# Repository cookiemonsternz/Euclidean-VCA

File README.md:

# ANTANTEATEREATER

Antanteatereater is a guitar/bass effect pedal which consists of a euclidean sequencer running into a VCA. It is based around the digital HY-ESG plugin, but using an analog envelope generator and vca, as well as being in a physical format.

The euclidean sequencer runs on an MCU, in this case an arduino nano, simply because I had one lying around. The pedal has 7 controllable inputs:

-   On/Off Button
-   Tap Tempo Button (Sequencer syncs to this)
-   Envelope Attack
-   Envelope Release
-   Step (Total number of steps per cycle)
-   Pulse (Number of steps per cycle which are on)
-   Rotate (Offset of the cycle)

The project is named after the design I chose for it, which is an ant-anteater-eater, aka an ant which eats anteaters :)

### The Why -

When I make music, my absolutely most used plugin is HY-ESG. I find it super versatile and very handy for adding some rhythm to otherwise static pads and other noise. I wanted a way to use this effect in live performances, and given I don't like to have things running through my laptop on stage (due to reliability), and the fact that using it requires a lot of extra hardware, I decided to make a version of it that just worked like any regular guitar pedal.

### Pictures!

The wooden top plate will be laser cut and engraved:

#### Wiring Diagram

(Im so sorry)

| Item             | Part Name          | Quantity          | Source       | Link                                                                                                                                                                                                                                                                                                                                                                                                                                                                                                                                                                                                                                                                                                                                                                                          | Unit Cost (USD) | Total Cost (USD) | Notes                                                             |
| ---------------- | ------------------ | ----------------- | ------------ | --------------------------------------------------------------------------------------------------------------------------------------------------------------------------------------------------------------------------------------------------------------------------------------------------------------------------------------------------------------------------------------------------------------------------------------------------------------------------------------------------------------------------------------------------------------------------------------------------------------------------------------------------------------------------------------------------------------------------------------------------------------------------------------------- | --------------- | ---------------- | ----------------------------------------------------------------- |
| U1, U2, U3       | Op Amp \(LM358DR2G | 3                 | JLCPCB Parts | [Op Amps](https://jlcpcb.com/partdetail/onsemi-LM358DR2G/C7950)                                                                                                                                                                                                                                                                                                                                                                                                                                                                                                                                                                                                                                                                                                                               | 0\.08           | 0\.24            |                                                                   |
| R                | Resistors          | 23                | JLCPCB Parts | JLCPCB Basic                                                                                                                                                                                                                                                                                                                                                                                                                                                                                                                                                                                                                                                                                                                                                                                  | Minimal         | Minimal          |                                                                   |
| D                | Diodes             | 4                 | JLCPCB Parts | [Diodes](https://jlcpcb.com/partdetail/65968-SM4007PL/C64898)                                                                                                                                                                                                                                                                                                                                                                                                                                                                                                                                                                                                                                                                                                                                 | Minimal         | Minimal          |                                                                   |
| C                | Capacitors         | 9                 | JLCPCB Parts | JLCPCB Basic                                                                                                                                                                                                                                                                                                                                                                                                                                                                                                                                                                                                                                                                                                                                                                                  | Minimal         | Minimal          |                                                                  |
| NA                | Board + PCBA Fees         | 1                 | JLCPCB | NA                                                                                                                                                                                                                                                                                                                                                                                                                                                                                                                                                                                                                                                                                                                                                                                  | 16.80         | 16.80          |                                                                  |
| SW1\-SW3         | Rotary Encoders    | 3                 | Aliexpress   | [Rotary Encoders](https://www.aliexpress.com/item/1005008773438800.html?spm=a2g0o.productlist.main.4.6caf67db8wY43y&aem_p4p_detail=20251021225419728471436773700001126656&algo_pvid=33d9d21c-5db8-425e-b5e4-98c99a6a57ad&algo_exp_id=33d9d21c-5db8-425e-b5e4-98c99a6a57ad-3&pdp_ext_f=%7B%22order%22%3A%2244%22%2C%22eval%22%3A%221%22%2C%22fromPage%22%3A%22search%22%7D&pdp_npi=6%40dis%21USD%213.09%210.99%21%21%2121.93%217.05%21%40210319b717611124590108818eb1c8%2112000048927220926%21sea%21NZ%210%21ABX%211%210%21n_tag%3A-29910%3Bd%3Abeb8c3d2%3Bm03_new_user%3A-29895%3BpisId%3A5000000187461950&curPageLogUid=7pVJIb4zHbn9&utparam-url=scene%3Asearch%7Cquery_from%3A%7Cx_object_id%3A1005008773438800%7C_p_origin_prod%3A&search_p4p_id=20251021225419728471436773700001126656_1) | NA              | 3\.32            | Batch of five                                                     |
| RV3, RV4         | Potentiometers     | 2                 | Aliexpress   | [Potentiometers](https://www.aliexpress.com/item/1005009279286977.html?spm=a2g0o.productlist.main.9.3d663775RNmcx3&algo_pvid=c2dfce7a-b170-4a07-a5f8-63d1f6594e30&algo_exp_id=c2dfce7a-b170-4a07-a5f8-63d1f6594e30-8&pdp_ext_f=%7B%22order%22%3A%22-1%22%2C%22eval%22%3A%221%22%2C%22fromPage%22%3A%22search%22%7D&pdp_npi=6%40dis%21USD%212.12%211.84%21%21%2115.00%2113.05%21%402101cb9417610761771086047ea9d2%2112000048591374661%21sea%21NZ%210%21ABX%211%210%21n_tag%3A-29910%3Bd%3Abeb8c3d2%3Bm03_new_user%3A-29895&curPageLogUid=NX8whLlntUPv&utparam-url=scene%3Asearch%7Cquery_from%3A%7Cx_object_id%3A1005009279286977%7C_p_origin_prod%3A#nav-specification)                                                                                                                       | NA              | 2\.12            | Batch of two                                                      |
| VR1, VR2         | Trim Pots          | 2                 | Aliexpress   | [Trim Pots](https://www.aliexpress.com/item/1005008933366467.html?spm=a2g0o.productlist.main.2.5d6e181cLNm8IK&algo_pvid=6d7d86ed-1912-4824-8d80-b0a5bc65a905&algo_exp_id=6d7d86ed-1912-4824-8d80-b0a5bc65a905-1&pdp_ext_f=%7B%22order%22%3A%22-1%22%2C%22eval%22%3A%221%22%2C%22fromPage%22%3A%22search%22%7D&pdp_npi=6%40dis%21USD%212.50%212.50%21%21%212.50%212.50%21%402101d49617611126241312153e49b8%2112000047259060180%21sea%21NZ%210%21ABX%211%210%21n_tag%3A-29910%3Bd%3Abeb8c3d2%3Bm03_new_user%3A-29895&curPageLogUid=RflDh2KpwnZy&utparam-url=scene%3Asearch%7Cquery_from%3A%7Cx_object_id%3A1005008933366467%7C_p_origin_prod%3A)                                                                                                                                                | NA              | 2\.5             | Batch of ten                                                      |
| Q1\-Q3           | Transistor         | 3                 | Aliexpress   | [Transistors](https://www.aliexpress.com/item/1005009709874835.html?spm=a2g0o.productlist.main.4.7c812343vu2ybN&aem_p4p_detail=20251021225812789141495238000001136822&algo_pvid=4b2647f9-e07e-481b-9028-46523c268ebd&algo_exp_id=4b2647f9-e07e-481b-9028-46523c268ebd-3&pdp_ext_f=%7B%22order%22%3A%2211%22%2C%22eval%22%3A%221%22%2C%22fromPage%22%3A%22search%22%7D&pdp_npi=6%40dis%21USD%211.12%211.12%21%21%211.12%211.12%21%402101f41a17611126920528685e99d7%2112000049920194524%21sea%21NZ%210%21ABX%211%210%21n_tag%3A-29910%3Bd%3Abeb8c3d2%3Bm03_new_user%3A-29895&curPageLogUid=lQghAouqlrHS&utparam-url=scene%3Asearch%7Cquery_from%3A%7Cx_object_id%3A1005009709874835%7C_p_origin_prod%3A&search_p4p_id=20251021225812789141495238000001136822_1)                                 | NA              | 1\.12            | Batch of 100 \(genuinely could not find smaller batch for cheap\) |
| NA               | 3PDT Switch        | 1                 | Aliexpress   | [3PDT Switch](https://www.aliexpress.com/item/727448148.html?spm=a2g0o.productlist.main.4.28ec52a9ZakJT4&aem_p4p_detail=202510212300455824725483349480001149988&algo_pvid=ceacb239-3ac1-475d-937f-75835e5627ed&algo_exp_id=ceacb239-3ac1-475d-937f-75835e5627ed-3&pdp_ext_f=%7B%22order%22%3A%2240%22%2C%22eval%22%3A%221%22%2C%22fromPage%22%3A%22search%22%7D&pdp_npi=6%40dis%21USD%213.84%210.99%21%21%213.84%210.99%21%402101f4dc17611128452705308edac3%2112000030303983184%21sea%21NZ%210%21ABX%211%210%21n_tag%3A-29910%3Bd%3Abeb8c3d2%3Bm03_new_user%3A-29895%3BpisId%3A5000000187461950&curPageLogUid=sKd94htJ7kvc&utparam-url=scene%3Asearch%7Cquery_from%3A%7Cx_object_id%3A727448148%7C_p_origin_prod%3A&search_p4p_id=202510212300455824725483349480001149988_1)                  | 3\.84           | 3\.84            |                                                                   |
| NA               | Momentary Switch   | 1                 | Aliexpress   | [Momentary Switch](https://www.aliexpress.com/item/1042107033.html?spm=a2g0o.productlist.main.8.41af1dc859ArZ6&aem_p4p_detail=2025102121464812556454111558440001085905&algo_pvid=17cf606d-b891-4a9e-a760-20d0d980f9b5&algo_exp_id=17cf606d-b891-4a9e-a760-20d0d980f9b5-7&pdp_ext_f=%7B%22order%22%3A%2244%22%2C%22eval%22%3A%221%22%2C%22fromPage%22%3A%22search%22%7D&pdp_npi=6%40dis%21USD%215.04%210.99%21%21%215.04%210.99%21%402103212b17611084085731627e89c9%2165952300265%21sea%21NZ%210%21ABX%211%210%21n_tag%3A-29910%3Bd%3Abeb8c3d2%3Bm03_new_user%3A-29895%3BpisId%3A5000000187461950&curPageLogUid=L5PGqnLCVdrA&utparam-url=scene%3Asearch%7Cquery_from%3A%7Cx_object_id%3A1042107033%7C_p_origin_prod%3A&search_p4p_id=2025102121464812556454111558440001085905_2)               | 5\.04           | 5\.04            | Looking for cheaper                                               |
| NA               | Enclosure          | 1                 | Aliexpress   | [Enclosure](https://www.aliexpress.com/item/1005008394958533.html?spm=a2g0o.productlist.main.9.39ae5bf4eggbWM&algo_pvid=1afa3e84-7a6b-462a-b49c-132afbac5897&algo_exp_id=1afa3e84-7a6b-462a-b49c-132afbac5897-8&pdp_ext_f=%7B%22order%22%3A%229%22%2C%22eval%22%3A%221%22%2C%22fromPage%22%3A%22search%22%7D&pdp_npi=6%40dis%21USD%213.59%212.69%21%21%2125.43%2119.07%21%402101f00e17611130054364209ea975%2112000044840709308%21sea%21NZ%210%21ABX%211%210%21n_tag%3A-29910%3Bd%3Abeb8c3d2%3Bm03_new_user%3A-29895&curPageLogUid=nIHeB34yhSRQ&utparam-url=scene%3Asearch%7Cquery_from%3A%7Cx_object_id%3A1005008394958533%7C_p_origin_prod%3A)                                                                                                                                               | 3\.59           | 3\.59            | Just using bottom half                                            |
| Total Cost       |                    |                   |              |                                                                                                                                                                                                                                                                                                                                                                                                                                                                                                                                                                                                                                                                                                                                                                                               |                 | 38\.57           |                                                                   |
| \-               | \-                 | \-                | \-           | \-                                                                                                                                                                                                                                                                                                                                                                                                                                                                                                                                                                                                                                                                                                                                                                                            | \-              | \-               | \-                                                                |
| Item             | Part Name          | Quantity          | Source       | Link                                                                                                                                                                                                                                                                                                                                                                                                                                                                                                                                                                                                                                                                                                                                                                                          | Unit Cost       | Total Cost       | Notes                                                             |
| PCB              | PCB                | 5 \(2 assembled\) | JLCPCB       | NA                                                                                                                                                                                                                                                                                                                                                                                                                                                                                                                                                                                                                                                                                                                                                                                            | NA              | 28\.3            | Incl\. Shipping + Tax                                             |
| Aliexpress Parts | Aliexpress Parts   | NA                | Aliexpress   | NA                                                                                                                                                                                                                                                                                                                                                                                                                                                                                                                                                                                                                                                                                                                                                                                            | NA              | 35\.46           | Incl\. Shipping + Tax                                             |
| Total Cost       |                    |                   |              |                                                                                                                                                                                                                                                                                                                                                                                                                                                                                                                                                                                                                                                                                                                                                                                               |                 | 63\.76           |                                                                   |

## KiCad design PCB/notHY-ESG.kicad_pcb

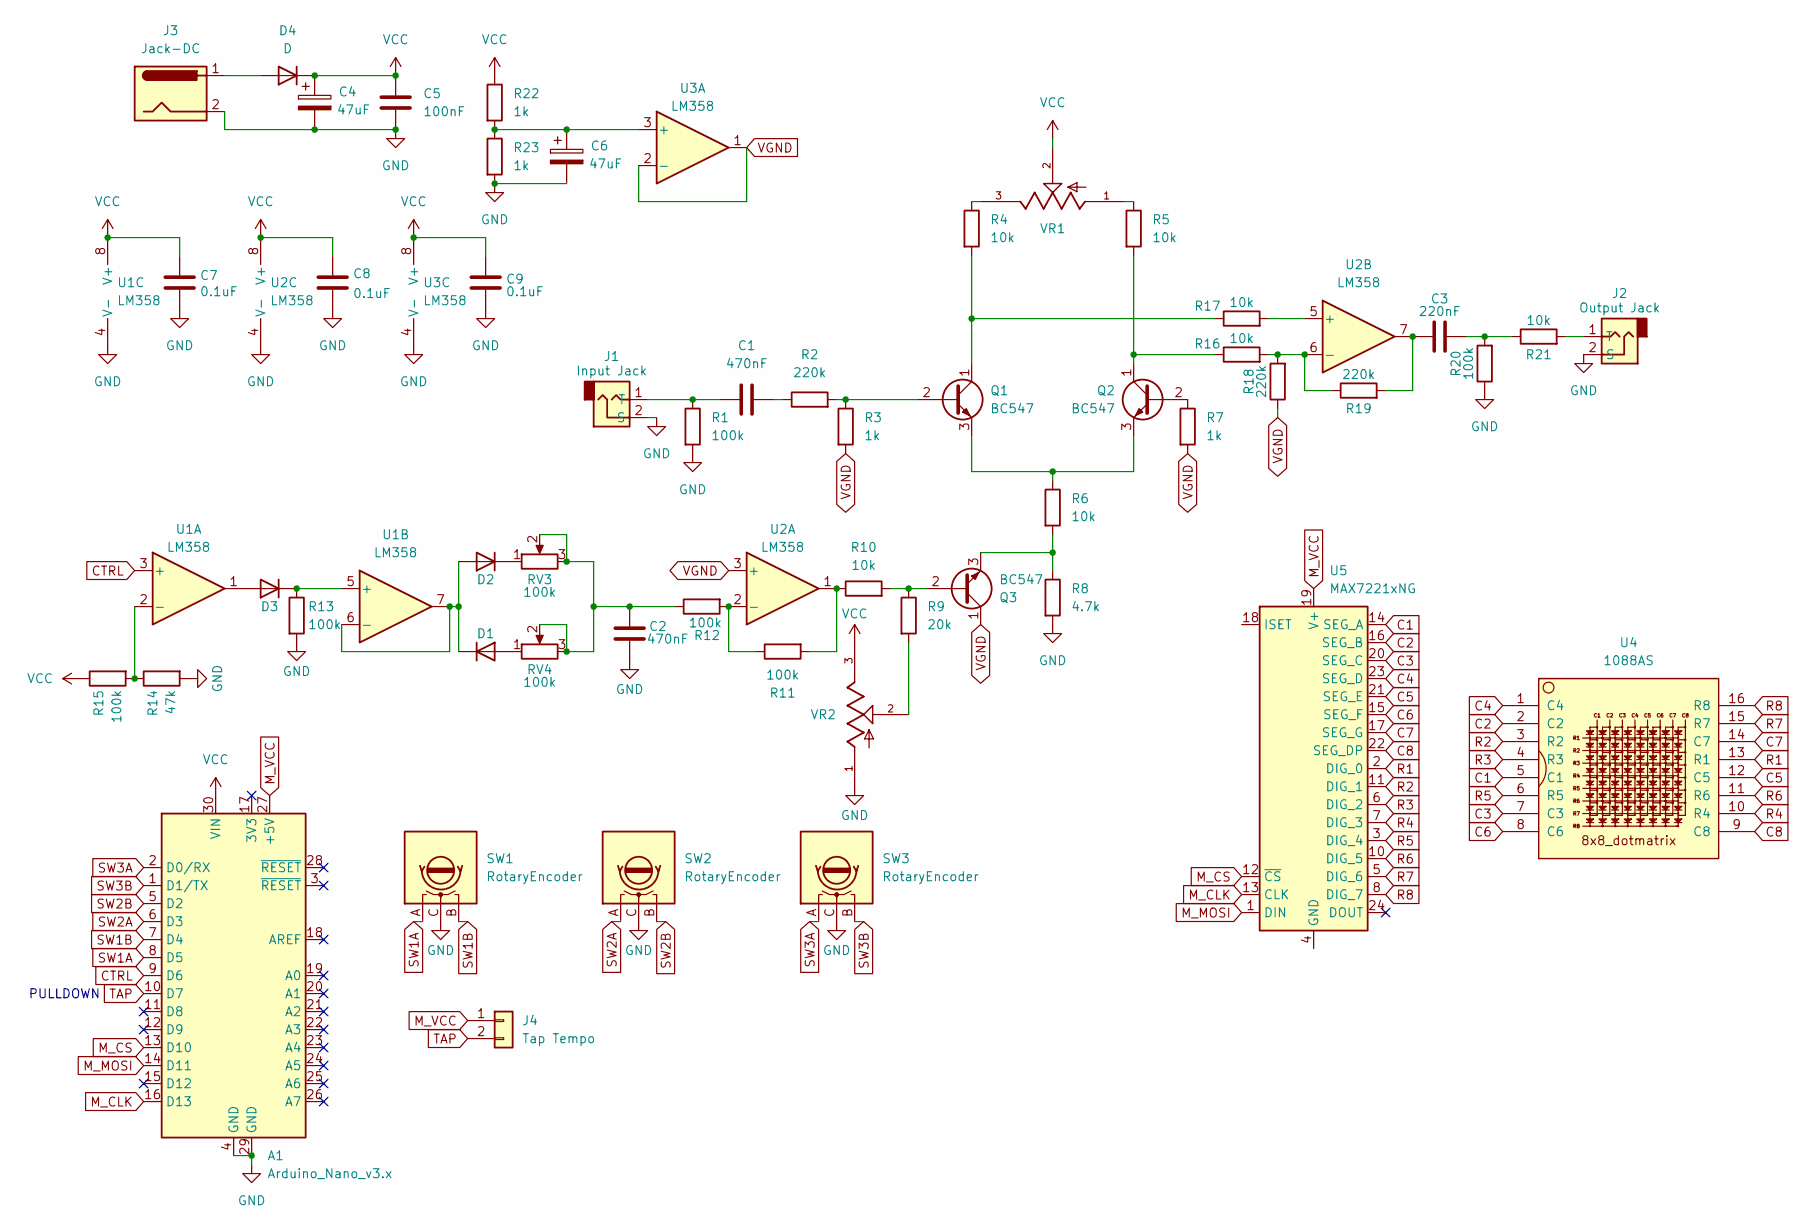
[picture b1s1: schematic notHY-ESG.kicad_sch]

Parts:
A1: Arduino_Nano_v3.x; Arduino_Nano
C1, C2: 470nF; C_0603_1608Metric_Pad1.08x0.95mm_HandSolder
C3: 220nF; C_0603_1608Metric_Pad1.08x0.95mm_HandSolder
C4, C6: 47uF; C_0805_2012Metric_Pad1.18x1.45mm_HandSolder
C5: 100nF; C_0603_1608Metric_Pad1.08x0.95mm_HandSolder
C7, C8, C9: 0.1uF; C_0603_1608Metric_Pad1.08x0.95mm_HandSolder
D1, D2, D3, D4: D; D_SOD-123F
J1: Input Jack; PinSocket_1x02_P2.54mm_Vertical
J2: Output Jack; PinSocket_1x02_P2.54mm_Vertical
J3: Jack-DC; PinSocket_1x02_P2.54mm_Vertical
J4: Tap Tempo; PinSocket_1x02_P2.54mm_Vertical
Q1, Q2, Q3: BC547; TO-92_Inline
R1, R11, R12, R13, R15, R20: 100k; R_0402_1005Metric_Pad0.72x0.64mm_HandSolder
R2, R18, R19: 220k; R_0603_1608Metric
R3, R7, R22, R23: 1k; R_0402_1005Metric_Pad0.72x0.64mm_HandSolder
R4, R5, R6, R10, R16, R17, R21: 10k; R_0402_1005Metric_Pad0.72x0.64mm_HandSolder
R8: 4.7k; R_0402_1005Metric_Pad0.72x0.64mm_HandSolder
R9: 20k; R_0402_1005Metric_Pad0.72x0.64mm_HandSolder
R14: 47k; R_0402_1005Metric_Pad0.72x0.64mm_HandSolder
RV3, RV4: 100k; Potentiometer_Alps_RK09L_Single_Vertical
SW1, SW2, SW3: RotaryEncoder; RotaryEncoder_Alps_EC11E-Switch_Vertical_H20mm
U1, U2, U3: LM358; SOIC127P600X175-8N
U4: 1088AS; LED_1088_Pin_Header
U5: MAX7221xNG; DIP-24_W7.62mm
VR1, VR2: 3362P-1-254LF; TRIM_3362P-1-254LF; PARTREV 08/26/10

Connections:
C1: U4.5 (C1), U5.14 (SEG_A)
C2: U4.2 (C2), U5.16 (SEG_B)
C3: U4.7 (C3), U5.20 (SEG_C)
C4: U4.1 (C4), U5.23 (SEG_D)
C5: U4.12 (C5), U5.21 (SEG_E)
C6: U4.8 (C6), U5.15 (SEG_F)
C7: U4.14 (C7), U5.17 (SEG_G)
C8: U4.9 (C8), U5.22 (SEG_DP)
CTRL: A1.9 (D6), U1.3 (+)
GND: A1.4 (GND), A1.29 (GND), C2.2, C4.2, C5.2, C6.2, C7.2, C8.2, C9.2, J1.2 (S), J2.2 (S), J3.2, R1.2, R8.2, R13.2, R14.2, R20.1, R23.2, SW1.C, SW2.C, SW3.C, U1.4 (V-), U2.4 (V-), U3.4 (V-), VR2.1
M_CLK: A1.16 (D13), U5.13 (CLK)
M_CS: A1.13 (D10), U5.12 (~CS)
M_MOSI: A1.14 (D11), U5.1 (DIN)
M_VCC: A1.27 (+5V), J4.1, U5.19 (V+)
unnamed: C1.2, R2.1
unnamed: C2.1, R12.1, RV3.2, RV3.3, RV4.2, RV4.3
unnamed: C3.1, R19.2, U2.7
unnamed: C3.2, R20.2, R21.1
unnamed: D1.2 (A), RV4.1
unnamed: D1.1 (K), D2.2 (A), U1.6 (-), U1.7
unnamed: D2.1 (K), RV3.1
unnamed: D3.2 (A), U1.1
unnamed: D3.1 (K), R13.1, U1.5 (+)
unnamed: D4.2 (A), J3.1
unnamed: C1.1, J1.1 (T), R1.1
unnamed: J2.1 (T), R21.2
unnamed: Q1.2 (B), R2.2, R3.1
unnamed: Q1.1 (C), R4.2, R17.1
unnamed: Q1.3 (E), Q2.3 (E), R6.1
unnamed: Q2.2 (B), R7.1
unnamed: Q2.1 (C), R5.2, R16.1
unnamed: Q3.2 (B), R9.1, R10.2
unnamed: Q3.3 (E), R6.2, R8.1
unnamed: R4.1, VR1.3
unnamed: R5.1, VR1.1
unnamed: R9.2, VR2.2
unnamed: R10.1, R11.2, U2.1
unnamed: R14.1, R15.2, U1.2 (-)
unnamed: R11.1, R12.2, U2.2 (-)
unnamed: R17.2, U2.5 (+)
unnamed: R16.2, R18.2, R19.1, U2.6 (-)
unnamed: C6.1, R22.2, R23.1, U3.3 (+)
unnamed: U5.4 (GND), U5.9 (GND)
R1: U4.13 (R1), U5.2 (DIG_0)
R2: U4.3 (R2), U5.11 (DIG_1)
R3: U4.4 (R3), U5.6 (DIG_2)
R4: U4.10 (R4), U5.7 (DIG_3)
R5: U4.6 (R5), U5.3 (DIG_4)
R6: U4.11 (R6), U5.10 (DIG_5)
R7: U4.15 (R7), U5.5 (DIG_6)
R8: U4.16 (R8), U5.8 (DIG_7)
SW1A: A1.8 (D5), SW1.A
SW1B: A1.7 (D4), SW1.B
SW2A: A1.6 (D3), SW2.A
SW2B: A1.5 (D2), SW2.B
SW3A: A1.2 (D0/RX), SW3.A
SW3B: A1.1 (D1/TX), SW3.B
TAP: A1.10 (D7), J4.2
VCC: A1.30 (VIN), C4.1, C5.1, C7.1, C8.1, C9.1, D4.1 (K), R15.1, R22.1, U1.8 (V+), U2.8 (V+), U3.8 (V+), VR1.2, VR2.3
VGND: Q3.1 (C), R3.2, R7.2, R18.1, U2.3 (+), U3.1, U3.2 (-)

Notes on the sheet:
PULLDOWN

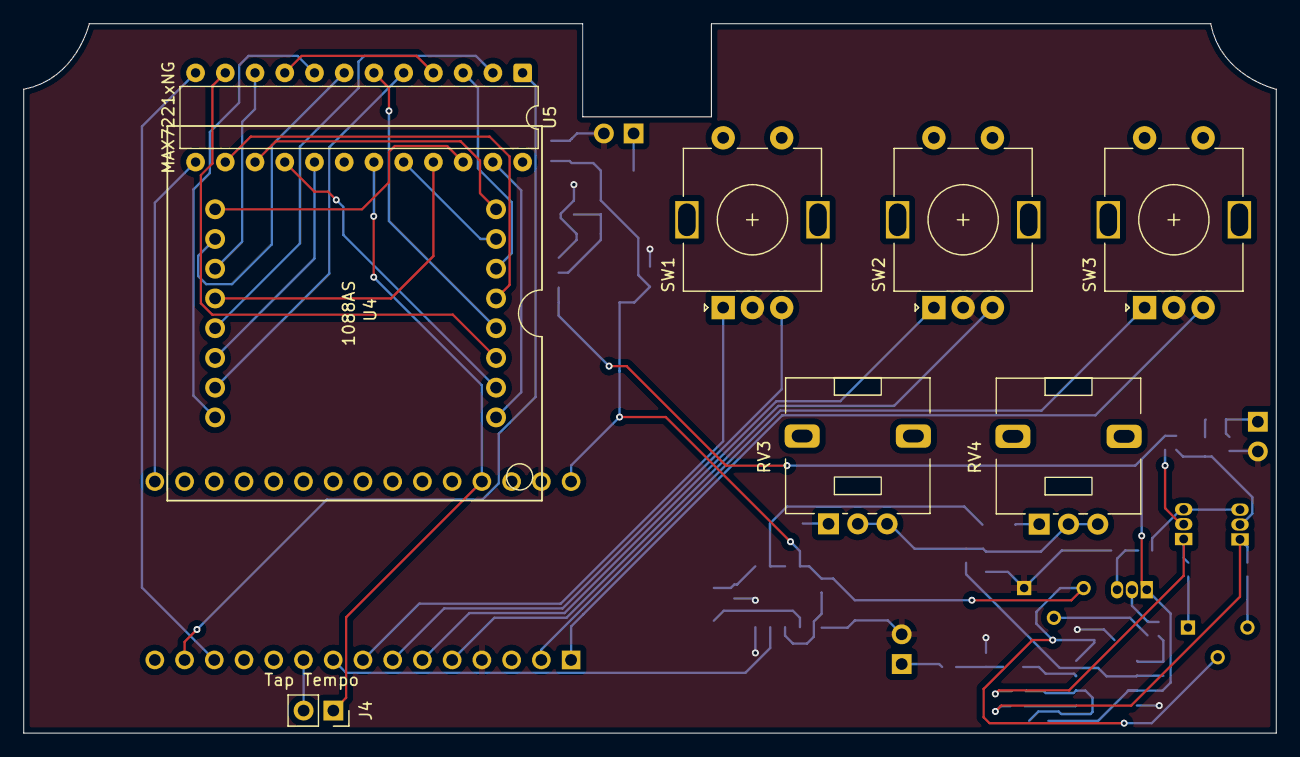
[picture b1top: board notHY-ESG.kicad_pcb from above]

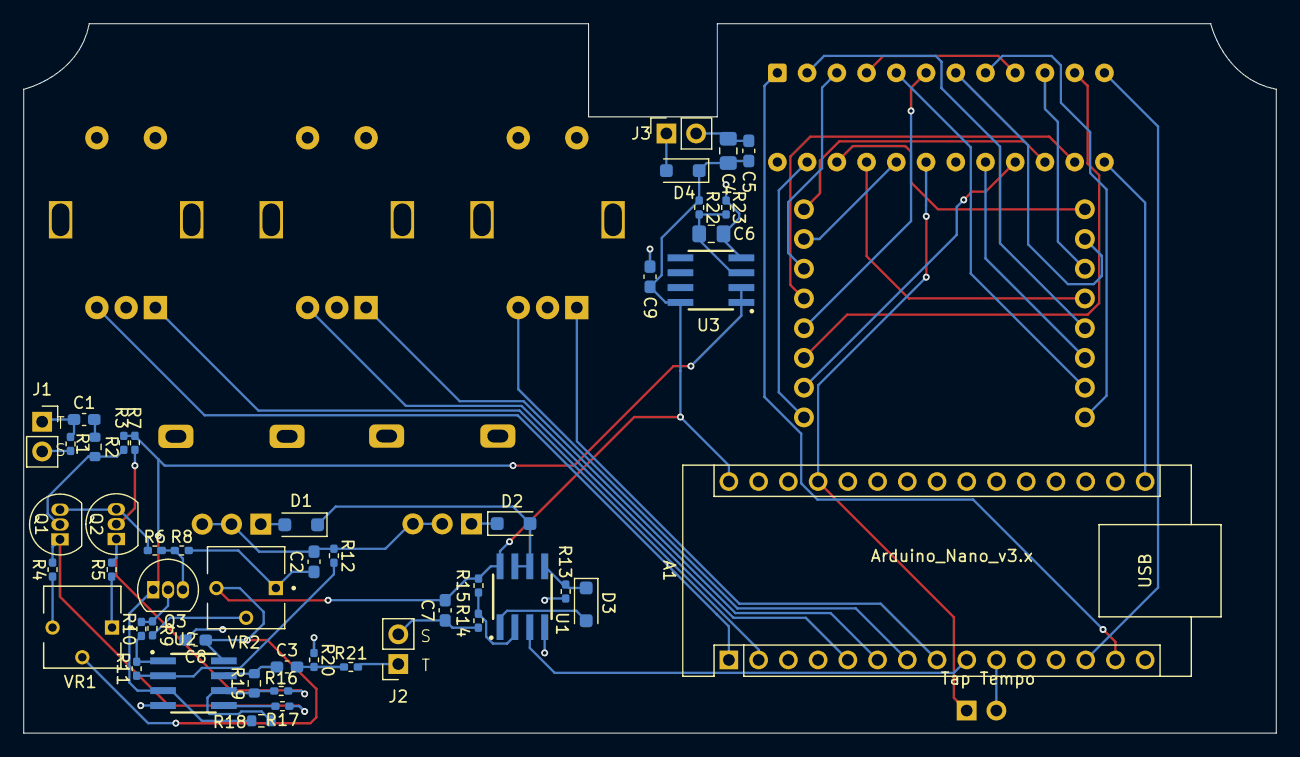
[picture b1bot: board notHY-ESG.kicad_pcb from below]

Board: 2 copper layers, 107.0 x 60.6 mm, 56 parts (48 on the bottom side), 60 nets.

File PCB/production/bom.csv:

Designator,Footprint,Quantity,Value,LCSC Part #
A1,Arduino_Nano,1,Arduino_Nano_v3.x,
"C1, C2",0603,2,470nF,
C3,0603,1,220nF,
"C4, C6",0805,2,47uF,
C5,0603,1,100nF,
"C7, C8, C9",0603,3,0.1uF,
"D1, D2, D3, D4",D_SOD-123F,4,D,
J1,PinSocket_1x02_P2.54mm_Vertical,1,Input Jack,
J2,PinSocket_1x02_P2.54mm_Vertical,1,Output Jack,
J3,PinSocket_1x02_P2.54mm_Vertical,1,Jack-DC,
J4,PinSocket_1x02_P2.54mm_Vertical,1,Tap Tempo,
"Q1, Q2, Q3",TO-92_Inline,3,BC547,
"R1, R11, R12, R13, R15, R20",0402,6,100k,
"R10, R16, R17, R21, R4, R5, R6",0402,7,10k,
R14,0402,1,47k,
"R18, R19, R2",0603,3,220k,
"R22, R23, R3, R7",0402,4,1k,
R8,0402,1,4.7k,
R9,0402,1,20k,
"RV3, RV4",Potentiometer_Alps_RK09L_Single_Vertical,2,100k,
"SW1, SW2, SW3",RotaryEncoder_Alps_EC11E-Switch_Vertical_H20mm,3,RotaryEncoder,
"U1, U2, U3",SOIC127P600X175-8N,3,LM358,
U4,LED_1088_Pin_Header,1,1088AS,
U5,DIP-24_W7.62mm,1,MAX7221xNG,
"VR1, VR2",TRIM_3362P-1-254LF,2,3362P-1-254LF,

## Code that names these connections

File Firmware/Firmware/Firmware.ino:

#include <Arduino.h>
#include <RotaryEncoder.h>
#include <LedControl.h>

#define CTRL_PIN 6 //D6
#define TAP_TEMPO_PIN 7 //D7
#define TAP_TEMPO_LED_PIN 12 //D12

#define SW1A_PIN 5 //D5
#define SW1B_PIN 4 //D4
#define SW2A_PIN 3 //D3
#define SW2B_PIN 2 //D2
#define SW3A_PIN 0 //D0
#define SW3B_PIN 1 //D1

#define CS_PIN 10 //D10
#define MOSI_PIN 11 //D11
#define CLK_PIN 13 //D13

// PARAMS
#define MIN_STEPS 1
#define MAX_STEPS 32


RotaryEncoder encoder_1(SW1A_PIN, SW1B_PIN, RotaryEncoder::LatchMode::TWO03);
RotaryEncoder encoder_2(SW2A_PIN, SW2B_PIN, RotaryEncoder::LatchMode::TWO03);
RotaryEncoder encoder_3(SW3A_PIN, SW3B_PIN, RotaryEncoder::LatchMode::TWO03);
int pos_1 = 0;
int pos_2 = 0;
int pos_3 = 0;

// Milliseconds
int interval = 1000;

int sequence[MAX_STEPS];

int clamp(int v, int lo, int hi) {
  const int t = v < lo ? lo : v;
  return t > hi ? hi : t;
}

void setup() {
  // put your setup code here, to run once:

}

void loop() {
  // Update encoders
  encoder_1.tick();
  int newPos = encoder_1.getPosition();
  if (pos_1 != newPos) pos_1 = newPos;
  pos_1 = clamp(pos_1, MIN_STEPS, MAX_STEPS);

  encoder_2.tick();
  newPos = encoder_2.getPosition();
  if (pos_2 != newPos) pos_2 = newPos;
  // Can't have more pulses than num steps
  pos_2 = clamp(pos_2, 0, MAX_STEPS);

  encoder_3.tick();
  newPos = encoder_3.getPosition();
  if (pos_3 != newPos) pos_3 = newPos;
  // No clamp for infinite rotation;
  // pos_3 = clamp(pos_3, 0, 127);

  calculate_euclidean_sequence(pos_1, pos_2, pos_3, sequence);

  static int idx = 0;
  idx = tick_euclidean(idx);
}

int increment_idx(int idx) {
  int newIndex = idx + 1;
  if (newIndex > MAX_STEPS) {
    newIndex = 0;
  }
  return newIndex;
}

int tick_euclidean(int idx) {
  static unsigned long previousMillis = 0;
  unsigned long currentMillis = millis();

  if (currentMillis - previousMillis >= interval) {
    previousMillis = currentMillis;

    bool currentState = sequence[idx];
    if (currentState) {
      digitalWrite(CTRL_PIN, HIGH);
    } else {
      digitalWrite(CTRL_PIN, LOW);
    }

    return increment_idx(idx);
  }
}

void rotate_seq(int *seq, int steps, int rotate) {
  int output[steps];
  int val = steps - rotate;

  for (int i = 0; i < steps; i++) {
    output[i] = seq[abs((i + val) % steps)];
  }

  for (int i = 0; i < steps; i++) {
      seq[i] = output[i];
  }
}

void calculate_euclidean_sequence(int steps, int pulses, int rotate, int* seq) {
  rotate += 1;
  int finalRhythm[steps];
  int bucket = 0;

  for (int i = 0; i < steps; i++) {
    bucket += pulses;
    if (bucket >= steps) {
      bucket -= steps;
      finalRhythm[i] = 1;
    } else {
      finalRhythm[i] = 0;
    }
  }

  if (rotate != 0) {
    rotate_seq(finalRhythm, steps, rotate);
  }

  for (int i = 0; i < steps; i++) {
      seq[i] = finalRhythm[i];
  }
}

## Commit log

2025-11-03 Init
2025-11-17 Add Readme and tidy up files
